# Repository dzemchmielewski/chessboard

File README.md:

# chessboard
Interactive chessboard

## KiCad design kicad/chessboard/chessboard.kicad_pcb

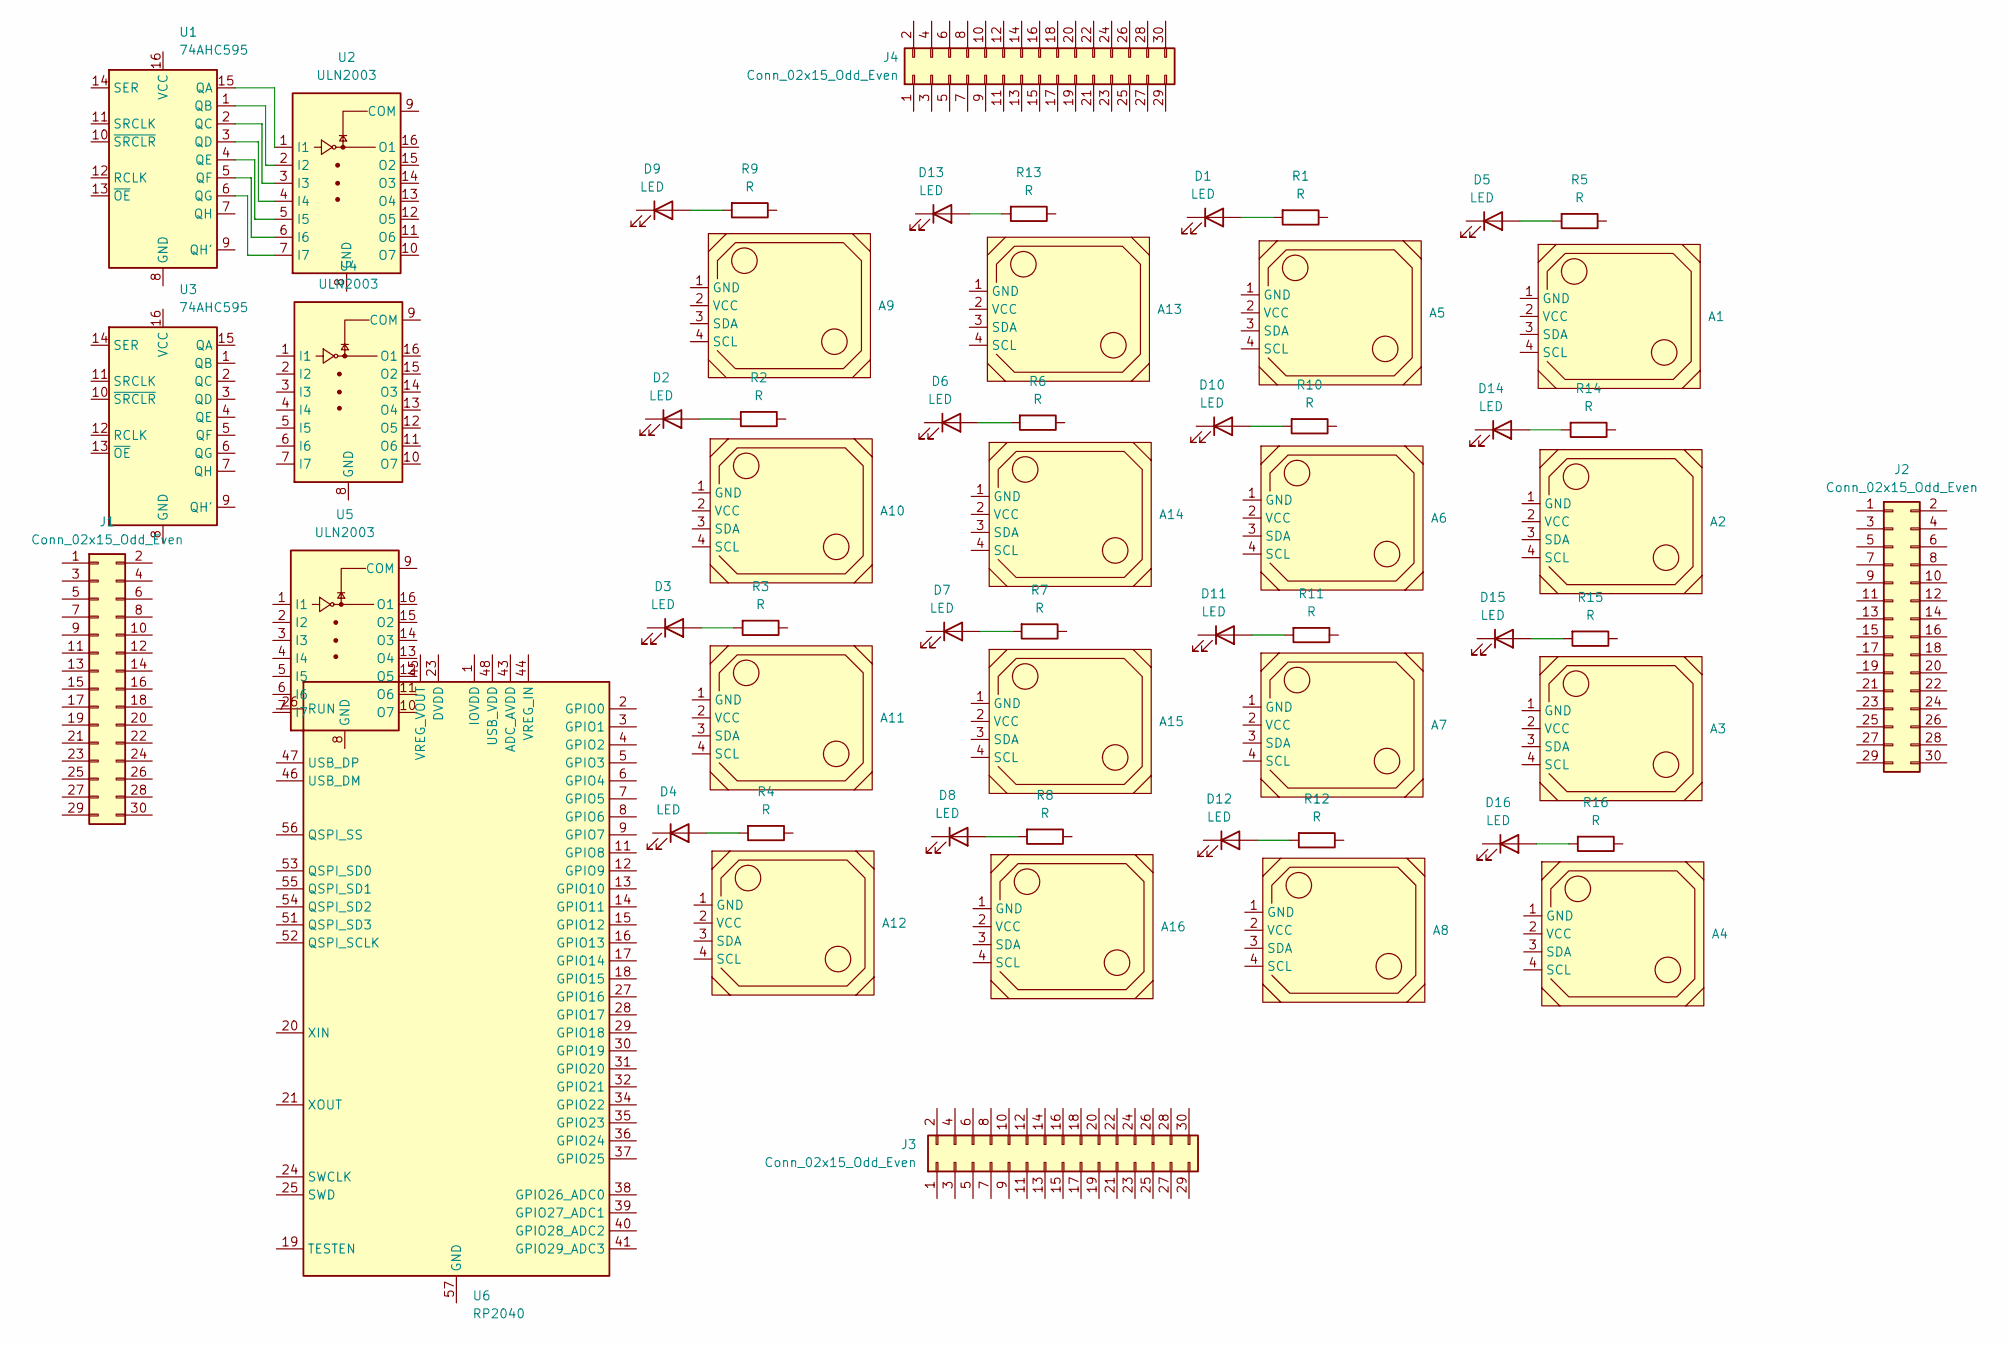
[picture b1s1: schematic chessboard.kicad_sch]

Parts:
A1, A2, A3, A4, A5, A6, A7, A8, A9, A10, A11, A12, A13, A14, A15, A16: PN532_NFC_module_v3
D1, D2, D3, D4, D5, D6, D7, D8, D9, D10, D11, D12, D13, D14, D15, D16: LED; LED_D3.0mm
J1, J2, J3, J4: Conn_02x15_Odd_Even; PinHeader_2x15_P2.54mm_Vertical
R1, R2, R3, R4, R5, R6, R7, R8, R9, R10, R11, R12, R13, R14, R15, R16: R; R_Axial_DIN0207_L6.3mm_D2.5mm_P7.62mm_Horizontal
U1, U3: 74AHC595; DIP-16_W7.62mm
U2: ULN2003; DIP-16_W7.62mm
U4, U5: ULN2003
U6: RP2040; QFN-56-1EP_7x7mm_P0.4mm_EP3.2x3.2mm

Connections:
unnamed: D1.2 (A), R1.2
unnamed: D2.2 (A), R2.2
unnamed: D3.2 (A), R3.2
unnamed: D4.2 (A), R4.2
unnamed: D5.2 (A), R5.2
unnamed: D6.2 (A), R6.2
unnamed: D7.2 (A), R7.2
unnamed: D8.2 (A), R8.2
unnamed: D9.2 (A), R9.2
unnamed: D10.2 (A), R10.2
unnamed: D11.2 (A), R11.2
unnamed: D12.2 (A), R12.2
unnamed: D13.2 (A), R13.2
unnamed: D14.2 (A), R14.2
unnamed: D15.2 (A), R15.2
unnamed: D16.2 (A), R16.2
unnamed: U1.15 (QA), U2.1 (I1)
unnamed: U1.1 (QB), U2.2 (I2)
unnamed: U1.2 (QC), U2.3 (I3)
unnamed: U1.3 (QD), U2.4 (I4)
unnamed: U1.4 (QE), U2.5 (I5)
unnamed: U1.5 (QF), U2.6 (I6)
unnamed: U1.6 (QG), U2.7 (I7)
unnamed: U6.1 (IOVDD), U6.10 (IOVDD), U6.22 (IOVDD), U6.33 (IOVDD), U6.42 (IOVDD), U6.49 (IOVDD)
unnamed: U6.23 (DVDD), U6.50 (DVDD)

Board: 2 copper layers, 55 parts (0 on the bottom side), 23 nets, no tracks yet.

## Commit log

2024-07-05 Initial - RP Pico 16-fields board reader
